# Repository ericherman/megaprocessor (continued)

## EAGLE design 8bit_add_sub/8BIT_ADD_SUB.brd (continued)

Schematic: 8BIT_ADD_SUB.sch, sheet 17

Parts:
D109, D110, D111, D112, D113, D114, D115, D116, D117: L-1334SRT; LED3MM
Q157, Q158, Q159, Q160, Q161, Q162, Q163, Q164, Q165: 2N7000; TO92-DGS
R181, R183, R186, R188, R191, R193: 10k; R_P2INCH
R182, R184, R185, R187, R189, R190, R192, R194, R195: 470; R_P2INCH

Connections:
+5V: D109.A, D110.A, D111.A, D112.A, D113.A, D114.A, D115.A, D116.A, D117.A, R181.2, R183.2, R186.2, R188.2, R191.2, R193.2; also elsewhere on the board
ADD_R4: Q158.G; also elsewhere on the board
ADD_R4_N: R185.1; also elsewhere on the board
CRY3: Q157.G; also elsewhere on the board
CRY3_N: R184.1; also elsewhere on the board
CRY4: Q162.D, R188.1; also elsewhere on the board
CRY4_N: Q160.D, Q161.D, Q162.G, R186.1, R187.1; also elsewhere on the board
GND: Q158.S, Q159.S, Q160.S, Q161.S, Q162.S, Q164.S, Q165.S; also elsewhere on the board
INV_B4: Q163.G; also elsewhere on the board
INV_B4_N: R194.1; also elsewhere on the board
IN_A4: Q164.G; also elsewhere on the board
IN_A4_N: R195.1; also elsewhere on the board
unnamed: Q157.S, Q158.D
unnamed: D109.K (C), R182.2
unnamed: Q159.D, Q160.G, R183.1
unnamed: Q157.D, Q159.G, R181.1, R182.1, R189.1
unnamed: D111.K (C), R185.2
unnamed: D110.K (C), R184.2
unnamed: D112.K (C), R187.2
unnamed: D114.K (C), R190.2
unnamed: D113.K (C), R189.2
unnamed: Q163.S, Q164.D
unnamed: D115.K (C), R192.2
unnamed: Q161.G, Q165.D, R193.1
unnamed: Q163.D, Q165.G, R190.1, R191.1, R192.1
unnamed: D117.K (C), R195.2
unnamed: D116.K (C), R194.2

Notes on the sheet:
ADD/SUB Bit 4 carry generation
AND
LED Y
LED A
LED B

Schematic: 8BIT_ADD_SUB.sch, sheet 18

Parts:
D73, D74, D75, D76, D77, D78: L-1334SRT; LED3MM
Q109, Q110, Q111, Q112, Q113, Q114, Q115, Q116, Q117, Q118: 2N7000; TO92-DGS
R121, R123, R126, R128: 10k; R_P2INCH
R122, R124, R125, R127, R129, R130: 470; R_P2INCH

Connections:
+5V: D73.A, D74.A, D75.A, D76.A, D77.A, D78.A, R121.2, R123.2, R126.2, R128.2; also elsewhere on the board
ADD_R5: Q113.D, Q117.G, R123.1; also elsewhere on the board
ADD_R5_N: Q109.D, Q111.D, Q113.G, Q115.G, R121.1, R122.1, R130.1; also elsewhere on the board
CRY4: Q114.G; also elsewhere on the board
CRY4_N: Q116.G, R129.1; also elsewhere on the board
GND: Q110.S, Q112.S, Q113.S, Q115.S, Q117.S, Q118.S; also elsewhere on the board
INV_B5: Q109.G; also elsewhere on the board
INV_B5_N: Q111.G, R124.1; also elsewhere on the board
IN_A5: Q112.G; also elsewhere on the board
IN_A5_N: Q110.G, R125.1; also elsewhere on the board
unnamed: Q109.S, Q110.D
unnamed: Q111.S, Q112.D
unnamed: D73.K (C), R122.2
unnamed: D75.K (C), R125.2
unnamed: D74.K (C), R124.2
unnamed: Q114.S, Q115.D
unnamed: Q116.S, Q117.D
unnamed: D76.K (C), R127.2
unnamed: D78.K (C), R130.2
unnamed: D77.K (C), R129.2
Y5: Q118.D, R128.1; also elsewhere on the board
Y5_N: Q114.D, Q116.D, Q118.G, R126.1, R127.1; also elsewhere on the board

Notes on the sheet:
ADD/SUB bit 5 XORs.
XOR
LED A
LED B
LED Y

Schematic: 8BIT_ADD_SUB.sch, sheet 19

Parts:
D118, D119, D120, D121, D122, D123, D124, D125, D126: L-1334SRT; LED3MM
Q166, Q167, Q168, Q169, Q170, Q171, Q172, Q173, Q174: 2N7000; TO92-DGS
R196, R198, R201, R203, R206, R208: 10k; R_P2INCH
R197, R199, R200, R202, R204, R205, R207, R209, R210: 470; R_P2INCH

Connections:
+5V: D118.A, D119.A, D120.A, D121.A, D122.A, D123.A, D124.A, D125.A, D126.A, R196.2, R198.2, R201.2, R203.2, R206.2, R208.2; also elsewhere on the board
ADD_R5: Q167.G; also elsewhere on the board
ADD_R5_N: R200.1; also elsewhere on the board
CRY4: Q166.G; also elsewhere on the board
CRY4_N: R199.1; also elsewhere on the board
CRY5: Q171.D, R203.1; also elsewhere on the board
CRY5_N: Q169.D, Q170.D, Q171.G, R201.1, R202.1; also elsewhere on the board
GND: Q167.S, Q168.S, Q169.S, Q170.S, Q171.S, Q173.S, Q174.S; also elsewhere on the board
INV_B5: Q172.G; also elsewhere on the board
INV_B5_N: R209.1; also elsewhere on the board
IN_A5: Q173.G; also elsewhere on the board
IN_A5_N: R210.1; also elsewhere on the board
unnamed: Q166.S, Q167.D
unnamed: D118.K (C), R197.2
unnamed: Q168.D, Q169.G, R198.1
unnamed: Q166.D, Q168.G, R196.1, R197.1, R204.1
unnamed: D120.K (C), R200.2
unnamed: D119.K (C), R199.2
unnamed: D121.K (C), R202.2
unnamed: D123.K (C), R205.2
unnamed: D122.K (C), R204.2
unnamed: Q172.S, Q173.D
unnamed: D124.K (C), R207.2
unnamed: Q170.G, Q174.D, R208.1
unnamed: Q172.D, Q174.G, R205.1, R206.1, R207.1
unnamed: D126.K (C), R210.2
unnamed: D125.K (C), R209.2

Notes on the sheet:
ADD/SUB Bit 5 carry generation
AND
LED Y
LED A
LED B

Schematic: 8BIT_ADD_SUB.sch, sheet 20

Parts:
D79, D80, D81, D82, D83, D84: L-1334SRT; LED3MM
Q119, Q120, Q121, Q122, Q123, Q124, Q125, Q126, Q127, Q128: 2N7000; TO92-DGS
R131, R133, R136, R138: 10k; R_P2INCH
R132, R134, R135, R137, R139, R140: 470; R_P2INCH

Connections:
+5V: D79.A, D80.A, D81.A, D82.A, D83.A, D84.A, R131.2, R133.2, R136.2, R138.2; also elsewhere on the board
ADD_R6: Q123.D, Q127.G, R133.1; also elsewhere on the board
ADD_R6_N: Q119.D, Q121.D, Q123.G, Q125.G, R131.1, R132.1, R140.1; also elsewhere on the board
CRY5: Q124.G; also elsewhere on the board
CRY5_N: Q126.G, R139.1; also elsewhere on the board
GND: Q120.S, Q122.S, Q123.S, Q125.S, Q127.S, Q128.S; also elsewhere on the board
INV_B6: Q119.G; also elsewhere on the board
INV_B6_N: Q121.G, R134.1; also elsewhere on the board
IN_A6: Q122.G; also elsewhere on the board
IN_A6_N: Q120.G, R135.1; also elsewhere on the board
unnamed: Q119.S, Q120.D
unnamed: Q121.S, Q122.D
unnamed: D79.K (C), R132.2
unnamed: D81.K (C), R135.2
unnamed: D80.K (C), R134.2
unnamed: Q124.S, Q125.D
unnamed: Q126.S, Q127.D
unnamed: D82.K (C), R137.2
unnamed: D84.K (C), R140.2
unnamed: D83.K (C), R139.2
Y6: Q128.D, R138.1; also elsewhere on the board
Y6_N: Q124.D, Q126.D, Q128.G, R136.1, R137.1; also elsewhere on the board

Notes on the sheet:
ADD/SUB bit 6 XORs.
XOR
LED A
LED B
LED Y

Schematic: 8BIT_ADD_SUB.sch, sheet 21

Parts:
D127, D128, D129, D130, D131, D132, D133, D134, D135: L-1334SRT; LED3MM
Q175, Q176, Q177, Q178, Q179, Q180, Q181, Q182, Q183: 2N7000; TO92-DGS
R211, R213, R216, R218, R221, R223: 10k; R_P2INCH
R212, R214, R215, R217, R219, R220, R222, R224, R225: 470; R_P2INCH

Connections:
+5V: D127.A, D128.A, D129.A, D130.A, D131.A, D132.A, D133.A, D134.A, D135.A, R211.2, R213.2, R216.2, R218.2, R221.2, R223.2; also elsewhere on the board
ADD_R6: Q176.G; also elsewhere on the board
ADD_R6_N: R215.1; also elsewhere on the board
CRY5: Q175.G; also elsewhere on the board
CRY5_N: R214.1; also elsewhere on the board
CRY6: Q180.D, R218.1; also elsewhere on the board
CRY6_N: Q178.D, Q179.D, Q180.G, R216.1, R217.1; also elsewhere on the board
GND: Q176.S, Q177.S, Q178.S, Q179.S, Q180.S, Q182.S, Q183.S; also elsewhere on the board
INV_B6: Q181.G; also elsewhere on the board
INV_B6_N: R224.1; also elsewhere on the board
IN_A6: Q182.G; also elsewhere on the board
IN_A6_N: R225.1; also elsewhere on the board
unnamed: Q175.S, Q176.D
unnamed: D127.K (C), R212.2
unnamed: Q177.D, Q178.G, R213.1
unnamed: Q175.D, Q177.G, R211.1, R212.1, R219.1
unnamed: D129.K (C), R215.2
unnamed: D128.K (C), R214.2
unnamed: D130.K (C), R217.2
unnamed: D132.K (C), R220.2
unnamed: D131.K (C), R219.2
unnamed: Q181.S, Q182.D
unnamed: D133.K (C), R222.2
unnamed: Q179.G, Q183.D, R223.1
unnamed: Q181.D, Q183.G, R220.1, R221.1, R222.1
unnamed: D135.K (C), R225.2
unnamed: D134.K (C), R224.2

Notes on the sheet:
ADD/SUB Bit 6 carry generation
AND
LED Y
LED A
LED B

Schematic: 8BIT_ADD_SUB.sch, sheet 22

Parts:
D85, D86, D87, D88, D89, D90: L-1334SRT; LED3MM
Q129, Q130, Q131, Q132, Q133, Q134, Q135, Q136, Q137, Q138: 2N7000; TO92-DGS
R141, R143, R146, R148: 10k; R_P2INCH
R142, R144, R145, R147, R149, R150: 470; R_P2INCH

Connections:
+5V: D85.A, D86.A, D87.A, D88.A, D89.A, D90.A, R141.2, R143.2, R146.2, R148.2; also elsewhere on the board
ADD_R7: Q133.D, Q137.G, R143.1; also elsewhere on the board
ADD_R7_N: Q129.D, Q131.D, Q133.G, Q135.G, R141.1, R142.1, R150.1; also elsewhere on the board
CRY6: Q134.G; also elsewhere on the board
CRY6_N: Q136.G, R149.1; also elsewhere on the board
GND: Q130.S, Q132.S, Q133.S, Q135.S, Q137.S, Q138.S; also elsewhere on the board
INV_B7: Q129.G; also elsewhere on the board
INV_B7_N: Q131.G, R144.1; also elsewhere on the board
IN_A7: Q132.G; also elsewhere on the board
IN_A7_N: Q130.G, R145.1; also elsewhere on the board
unnamed: Q129.S, Q130.D
unnamed: Q131.S, Q132.D
unnamed: D85.K (C), R142.2
unnamed: D87.K (C), R145.2
unnamed: D86.K (C), R144.2
unnamed: Q134.S, Q135.D
unnamed: Q136.S, Q137.D
unnamed: D88.K (C), R147.2
unnamed: D90.K (C), R150.2
unnamed: D89.K (C), R149.2
Y7: Q138.D, R148.1; also elsewhere on the board
Y7_N: Q134.D, Q136.D, Q138.G, R146.1, R147.1; also elsewhere on the board

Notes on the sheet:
ADD/SUB bit 7 XORs.
XOR
LED A
LED B
LED Y

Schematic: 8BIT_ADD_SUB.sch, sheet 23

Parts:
D136, D137, D138, D139, D140, D141, D142, D143, D144: L-1334SRT; LED3MM
Q184, Q185, Q186, Q187, Q188, Q189, Q190, Q191, Q192: 2N7000; TO92-DGS
R226, R228, R231, R233, R236, R238: 10k; R_P2INCH
R227, R229, R230, R232, R234, R235, R237, R239, R240: 470; R_P2INCH

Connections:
+5V: D136.A, D137.A, D138.A, D139.A, D140.A, D141.A, D142.A, D143.A, D144.A, R226.2, R228.2, R231.2, R233.2, R236.2, R238.2; also elsewhere on the board
ADD_R7: Q185.G; also elsewhere on the board
ADD_R7_N: R230.1; also elsewhere on the board
CARRY_OUT: Q189.D, R233.1; also elsewhere on the board
CARRY_OUT_N: Q187.D, Q188.D, Q189.G, R231.1, R232.1
CRY6: Q184.G; also elsewhere on the board
CRY6_N: R229.1; also elsewhere on the board
GND: Q185.S, Q186.S, Q187.S, Q188.S, Q189.S, Q191.S, Q192.S; also elsewhere on the board
INV_B7: Q190.G; also elsewhere on the board
INV_B7_N: R239.1; also elsewhere on the board
IN_A7: Q191.G; also elsewhere on the board
IN_A7_N: R240.1; also elsewhere on the board
unnamed: Q184.S, Q185.D
unnamed: D136.K (C), R227.2
unnamed: Q186.D, Q187.G, R228.1
unnamed: Q184.D, Q186.G, R226.1, R227.1, R234.1
unnamed: D138.K (C), R230.2
unnamed: D137.K (C), R229.2
unnamed: D139.K (C), R232.2
unnamed: D141.K (C), R235.2
unnamed: D140.K (C), R234.2
unnamed: Q190.S, Q191.D
unnamed: D142.K (C), R237.2
unnamed: Q188.G, Q192.D, R238.1
unnamed: Q190.D, Q192.G, R235.1, R236.1, R237.1
unnamed: D144.K (C), R240.2
unnamed: D143.K (C), R239.2

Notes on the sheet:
ADD/SUB Bit 7 carry generation
AND
LED Y
LED A
LED B

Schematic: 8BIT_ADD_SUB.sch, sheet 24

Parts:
D154, D163, D164, D165, D166, D167, D168, D169, D170, D171, D172: L-1334SRT; LED3MM
Q209, Q210, Q211, Q212, Q213: 2N7000; TO92-DGS
R257, R268, R285, R287, R289: 10k; R_P2INCH
R258, R277, R278, R279, R280, R281, R282, R283, R284, R286, R288: 470; R_P2INCH

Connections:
+5V: D154.A, D163.A, D164.A, D165.A, D166.A, D167.A, D168.A, D169.A, D170.A, D171.A, D172.A, R257.2, R268.2, R285.2, R287.2, R289.2; also elsewhere on the board
CARRY_IN: Q213.D, R289.1; also elsewhere on the board
CARRY_IN_N: Q212.D, Q213.G, R285.1, R288.1; also elsewhere on the board
CARRY_IN_RAW: Q212.G; also elsewhere on the board
CARRY_OUT: Q211.G; also elsewhere on the board
CARRY_OUT_N2: Q211.D, R286.1, R287.1
DO_INVERT: Q210.D, R268.1; also elsewhere on the board
DO_INVERT_N: Q209.D, Q210.G, R257.1, R258.1; also elsewhere on the board
DO_INVERT_RAW: Q209.G; also elsewhere on the board
GND: Q209.S, Q210.S, Q211.S, Q212.S, Q213.S; also elsewhere on the board
unnamed: D154.K (C), R258.2
unnamed: D163.K (C), R277.2
unnamed: D171.K (C), R288.2
unnamed: D164.K (C), R278.2
unnamed: D165.K (C), R279.2
unnamed: D166.K (C), R280.2
unnamed: D167.K (C), R281.2
unnamed: D168.K (C), R282.2
unnamed: D169.K (C), R283.2
unnamed: D170.K (C), R284.2
unnamed: D172.K (C), R286.2
Y0_N: R277.1; also elsewhere on the board
Y1_N: R278.1; also elsewhere on the board
Y2_N: R279.1; also elsewhere on the board
Y3_N: R280.1; also elsewhere on the board
Y4_N: R281.1; also elsewhere on the board
Y5_N: R282.1; also elsewhere on the board
Y6_N: R283.1; also elsewhere on the board
Y7_N: R284.1; also elsewhere on the board

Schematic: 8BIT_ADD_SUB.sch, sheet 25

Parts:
J4: 30_HDR_LOCKING_RA

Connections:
GND: J4.1, J4.10, J4.19, J4.28; also elsewhere on the board
IN_A0: J4.2; also elsewhere on the board
IN_A1: J4.3; also elsewhere on the board
IN_A2: J4.4; also elsewhere on the board
IN_A3: J4.5; also elsewhere on the board
IN_A4: J4.6; also elsewhere on the board
IN_A5: J4.7; also elsewhere on the board
IN_A6: J4.8; also elsewhere on the board
IN_A7: J4.9; also elsewhere on the board
IN_B0: J4.11; also elsewhere on the board
IN_B1: J4.12; also elsewhere on the board
IN_B2: J4.13; also elsewhere on the board
IN_B3: J4.14; also elsewhere on the board
IN_B4: J4.15; also elsewhere on the board
IN_B5: J4.16; also elsewhere on the board
IN_B6: J4.17; also elsewhere on the board
IN_B7: J4.18; also elsewhere on the board
Y0: J4.20; also elsewhere on the board
Y1: J4.21; also elsewhere on the board
Y2: J4.22; also elsewhere on the board
Y3: J4.23; also elsewhere on the board
Y4: J4.24; also elsewhere on the board
Y5: J4.25; also elsewhere on the board
Y6: J4.26; also elsewhere on the board
Y7: J4.27; also elsewhere on the board

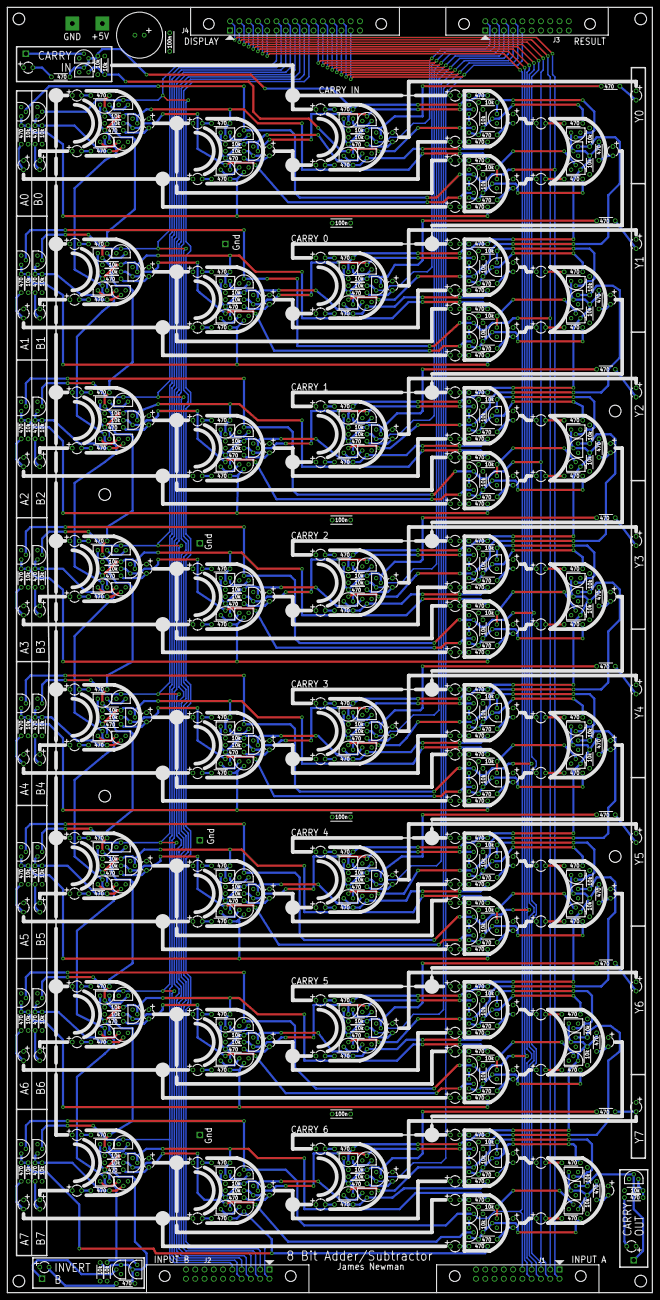
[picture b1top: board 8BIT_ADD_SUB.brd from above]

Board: 4 copper layers, 176.5 x 351.8 mm, 699 parts (0 on the bottom side), 372 nets.

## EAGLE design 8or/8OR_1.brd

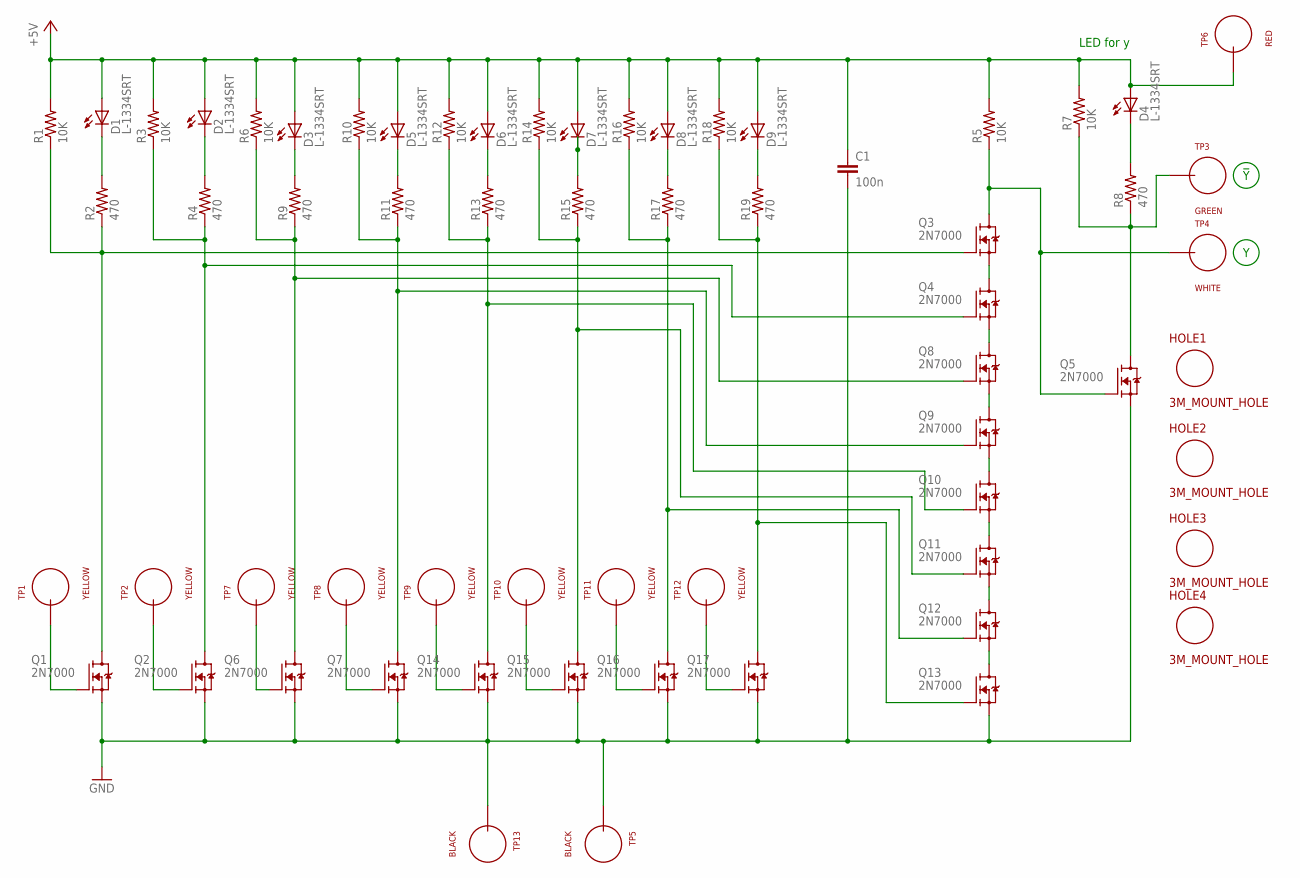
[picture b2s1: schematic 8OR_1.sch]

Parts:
C1: 100n; CAP_P2INCH
D1, D2, D3, D4, D5, D6, D7, D8, D9: L-1334SRT; LED3MM
HOLE1, HOLE2, HOLE3, HOLE4: 3M_MOUNT_HOLE; 3M_HOLE
Q1, Q2, Q3, Q4, Q5, Q6, Q7, Q8, Q9, Q10, Q11, Q12, Q13, Q14, Q15, Q16, Q17: 2N7000; TO92-DGS
R1, R3, R5, R6, R7, R10, R12, R14, R16, R18: 10K; R_P2INCH
R2, R4, R8, R9, R11, R13, R15, R17, R19: 470; R_P2INCH
TP1, TP2, TP7, TP8, TP9, TP10, TP11, TP12: YELLOW; TEST_LOOP
TP3: GREEN; TEST_LOOP
TP4: WHITE; TEST_LOOP
TP5, TP13: BLACK; TEST_LOOP
TP6: RED; TEST_LOOP

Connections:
+5V: C1.1, D1.A, D2.A, D3.A, D4.A, D5.A, D6.A, D7.A, D8.A, D9.A, R1.2, R3.2, R5.2, R6.2, R7.2, R10.2, R12.2, R14.2, R16.2, R18.2, TP6.P$1
GND: C1.2, Q1.S, Q2.S, Q5.S, Q6.S, Q7.S, Q13.S, Q14.S, Q15.S, Q16.S, Q17.S, TP5.P$1, TP13.P$1
unnamed: Q3.D, Q5.G, R5.1, TP4.P$1
unnamed: Q3.S, Q4.D
unnamed: D4.K (C), R8.2
unnamed: Q5.D, R7.1, R8.1, TP3.P$1
unnamed: D5.K (C), R11.2
unnamed: D2.K (C), R4.2
unnamed: Q4.S, Q8.D
unnamed: D1.K (C), R2.2
unnamed: Q1.D, Q3.G, R1.1, R2.1
unnamed: D3.K (C), R9.2
unnamed: Q1.G, TP1.P$1
unnamed: Q2.G, TP2.P$1
unnamed: Q6.D, Q8.G, R6.1, R9.1
unnamed: Q9.S, Q10.D
unnamed: Q10.S, Q11.D
unnamed: Q7.D, Q9.G, R10.1, R11.1
unnamed: Q2.D, Q4.G, R3.1, R4.1
unnamed: Q8.S, Q9.D
unnamed: D6.K (C), R13.2
unnamed: D7.K (C), R15.2
unnamed: D8.K (C), R17.2
unnamed: D9.K (C), R19.2
unnamed: Q10.G, Q14.D, R12.1, R13.1
unnamed: Q11.G, Q15.D, R14.1, R15.1
unnamed: Q12.G, Q16.D, R16.1, R17.1
unnamed: Q13.G, Q17.D, R18.1, R19.1
unnamed: Q11.S, Q12.D
unnamed: Q12.S, Q13.D
unnamed: Q17.G, TP12.P$1
unnamed: Q16.G, TP11.P$1
unnamed: Q15.G, TP10.P$1
unnamed: Q14.G, TP9.P$1
unnamed: Q7.G, TP8.P$1
unnamed: Q6.G, TP7.P$1

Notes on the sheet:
LED for y

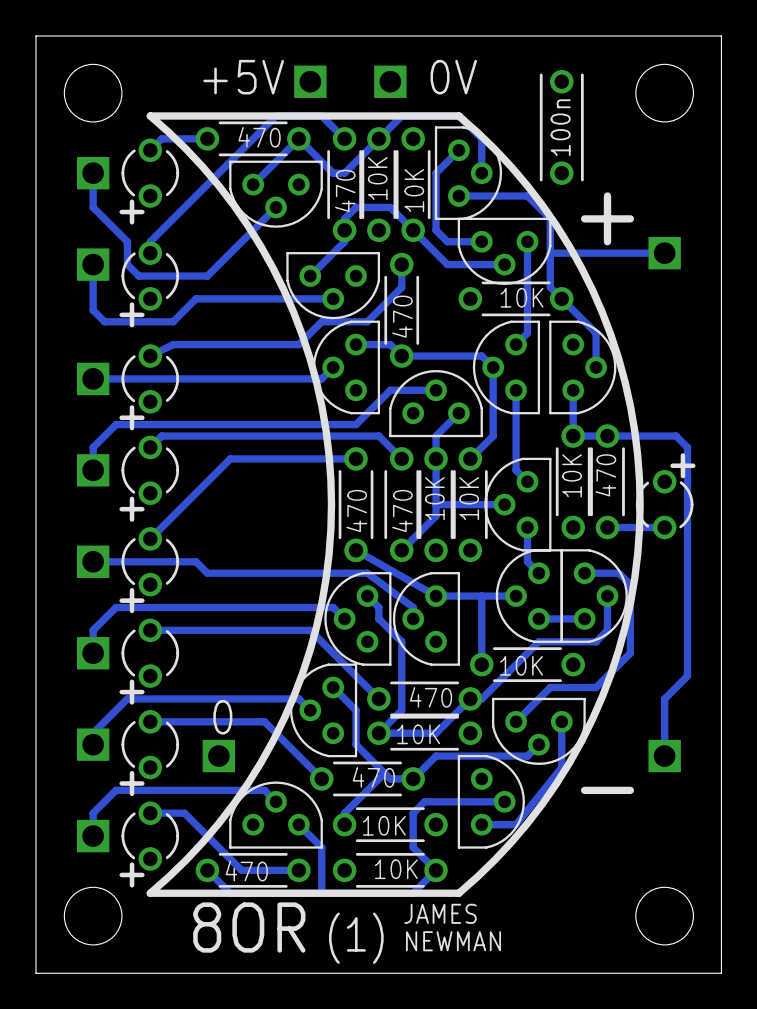
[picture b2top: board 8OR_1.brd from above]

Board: 4 copper layers, 38.1 x 52.1 mm, 63 parts (0 on the bottom side), 36 nets.

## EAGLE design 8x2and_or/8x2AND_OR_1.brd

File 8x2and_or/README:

8x2AND OR

Somehow when doing this board I messed up the power plane so it didn't
extend over the whole board. So there's a few wires underneath to sort
things out.

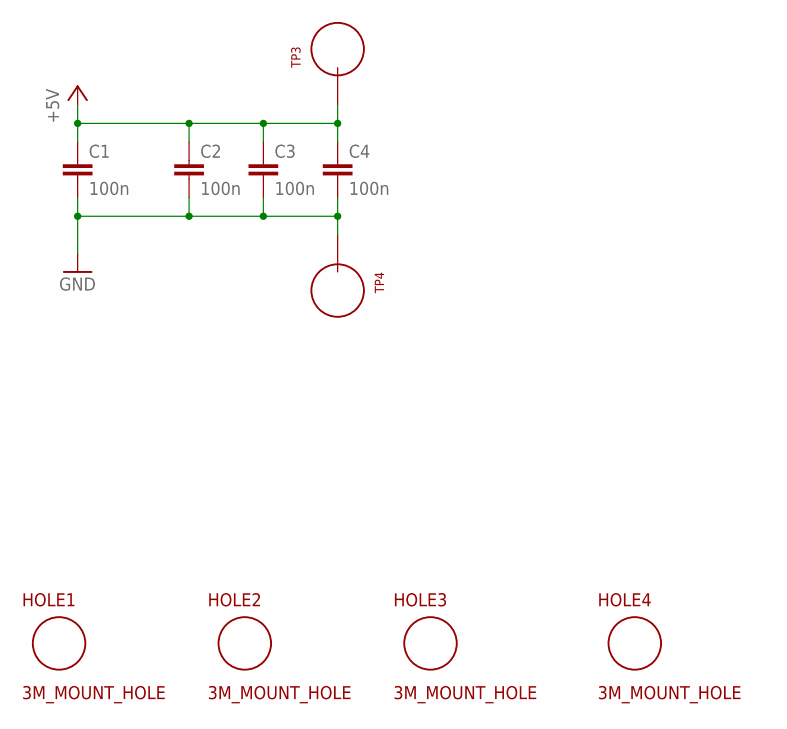
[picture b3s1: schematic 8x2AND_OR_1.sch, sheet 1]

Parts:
C1, C2, C3, C4: 100n; CAP_P2INCH
HOLE1, HOLE2, HOLE3, HOLE4: 3M_MOUNT_HOLE; 3M_HOLE
TP3, TP4: TEST_LOOP

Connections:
+5V: C1.1, C2.1, C3.1, C4.1, TP3.P$1; also elsewhere on the board
GND: C1.2, C2.2, C3.2, C4.2, TP4.P$1; also elsewhere on the board

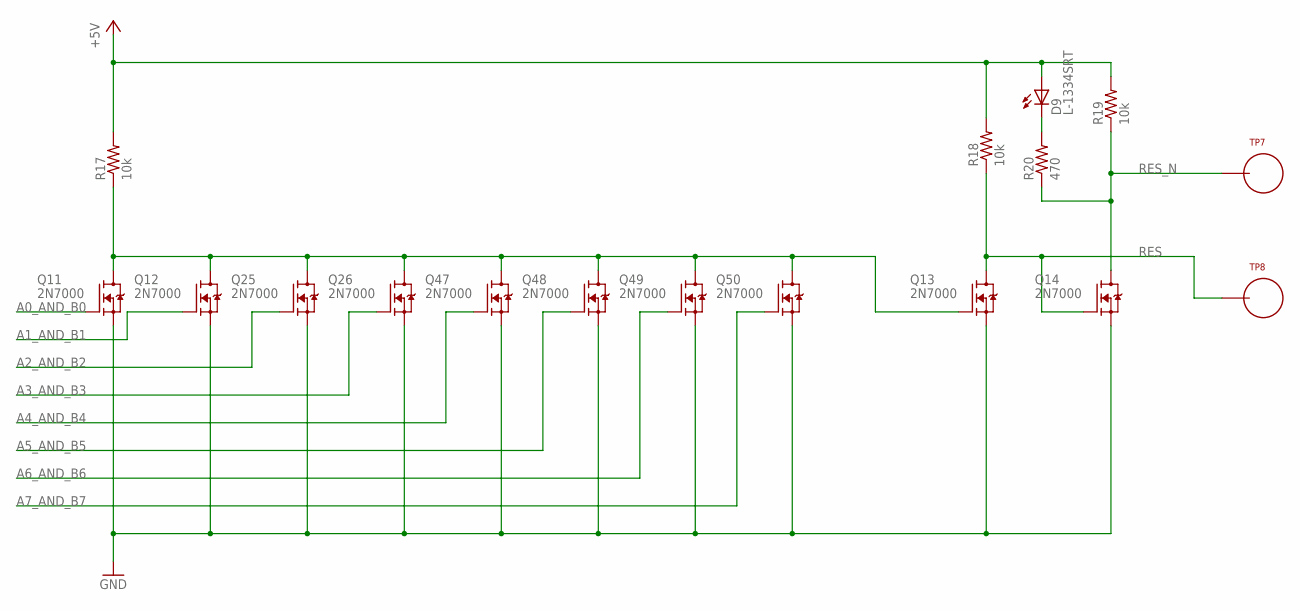
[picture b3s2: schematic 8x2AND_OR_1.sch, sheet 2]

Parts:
D9: L-1334SRT; LED3MM
Q11, Q12, Q13, Q14, Q25, Q26, Q47, Q48, Q49, Q50: 2N7000; TO92-DGS
R17, R18, R19: 10k; R_P2INCH
R20: 470; R_P2INCH
TP7, TP8: TEST_LOOP

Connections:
+5V: D9.A, R17.2, R18.2, R19.2; also elsewhere on the board
A0_AND_B0: Q11.G; also elsewhere on the board
A1_AND_B1: Q12.G; also elsewhere on the board
A2_AND_B2: Q25.G; also elsewhere on the board
A3_AND_B3: Q26.G; also elsewhere on the board
A4_AND_B4: Q47.G; also elsewhere on the board
A5_AND_B5: Q48.G; also elsewhere on the board
A6_AND_B6: Q49.G; also elsewhere on the board
A7_AND_B7: Q50.G; also elsewhere on the board
GND: Q11.S, Q12.S, Q13.S, Q14.S, Q25.S, Q26.S, Q47.S, Q48.S, Q49.S, Q50.S; also elsewhere on the board
unnamed: Q11.D, Q12.D, Q13.G, Q25.D, Q26.D, Q47.D, Q48.D, Q49.D, Q50.D, R17.1
unnamed: D9.K (C), R20.2
RES: Q13.D, Q14.G, R18.1, TP8.P$1
RES_N: Q14.D, R19.1, R20.1, TP7.P$1

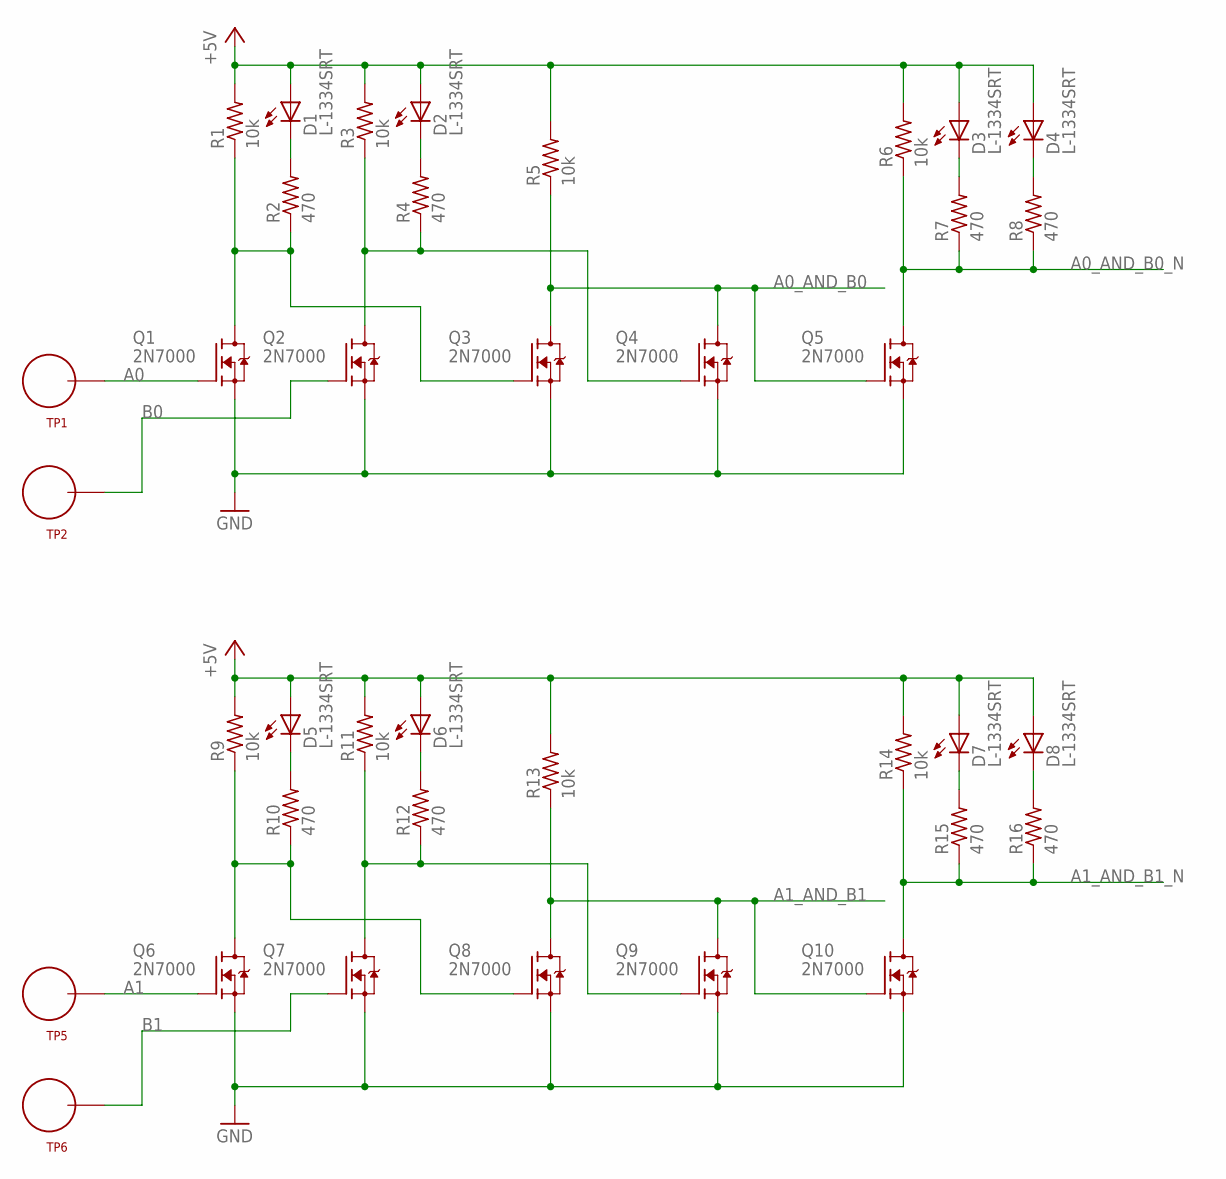
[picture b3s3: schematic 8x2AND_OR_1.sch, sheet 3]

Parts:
D1, D2, D3, D4, D5, D6, D7, D8: L-1334SRT; LED3MM
Q1, Q2, Q3, Q4, Q5, Q6, Q7, Q8, Q9, Q10: 2N7000; TO92-DGS
R1, R3, R5, R6, R9, R11, R13, R14: 10k; R_P2INCH
R2, R4, R7, R8, R10, R12, R15, R16: 470; R_P2INCH
TP1, TP2, TP5, TP6: TEST_LOOP

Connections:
+5V: D1.A, D2.A, D3.A, D4.A, D5.A, D6.A, D7.A, D8.A, R1.2, R3.2, R5.2, R6.2, R9.2, R11.2, R13.2, R14.2; also elsewhere on the board
A0: Q1.G, TP1.P$1
A0_AND_B0: Q3.D, Q4.D, Q5.G, R5.1; also elsewhere on the board
A0_AND_B0_N: Q5.D, R6.1, R7.1, R8.1
A1: Q6.G, TP5.P$1
A1_AND_B1: Q8.D, Q9.D, Q10.G, R13.1; also elsewhere on the board
A1_AND_B1_N: Q10.D, R14.1, R15.1, R16.1
B0: Q2.G, TP2.P$1
B1: Q7.G, TP6.P$1
GND: Q1.S, Q2.S, Q3.S, Q4.S, Q5.S, Q6.S, Q7.S, Q8.S, Q9.S, Q10.S; also elsewhere on the board
unnamed: D1.K (C), R2.2
unnamed: Q1.D, Q3.G, R1.1, R2.1
unnamed: D4.K (C), R8.2
unnamed: D2.K (C), R4.2
unnamed: Q2.D, Q4.G, R3.1, R4.1
unnamed: D5.K (C), R10.2
unnamed: Q6.D, Q8.G, R9.1, R10.1
unnamed: D6.K (C), R12.2
unnamed: D3.K (C), R7.2
unnamed: Q7.D, Q9.G, R11.1, R12.1
unnamed: D7.K (C), R15.2
unnamed: D8.K (C), R16.2

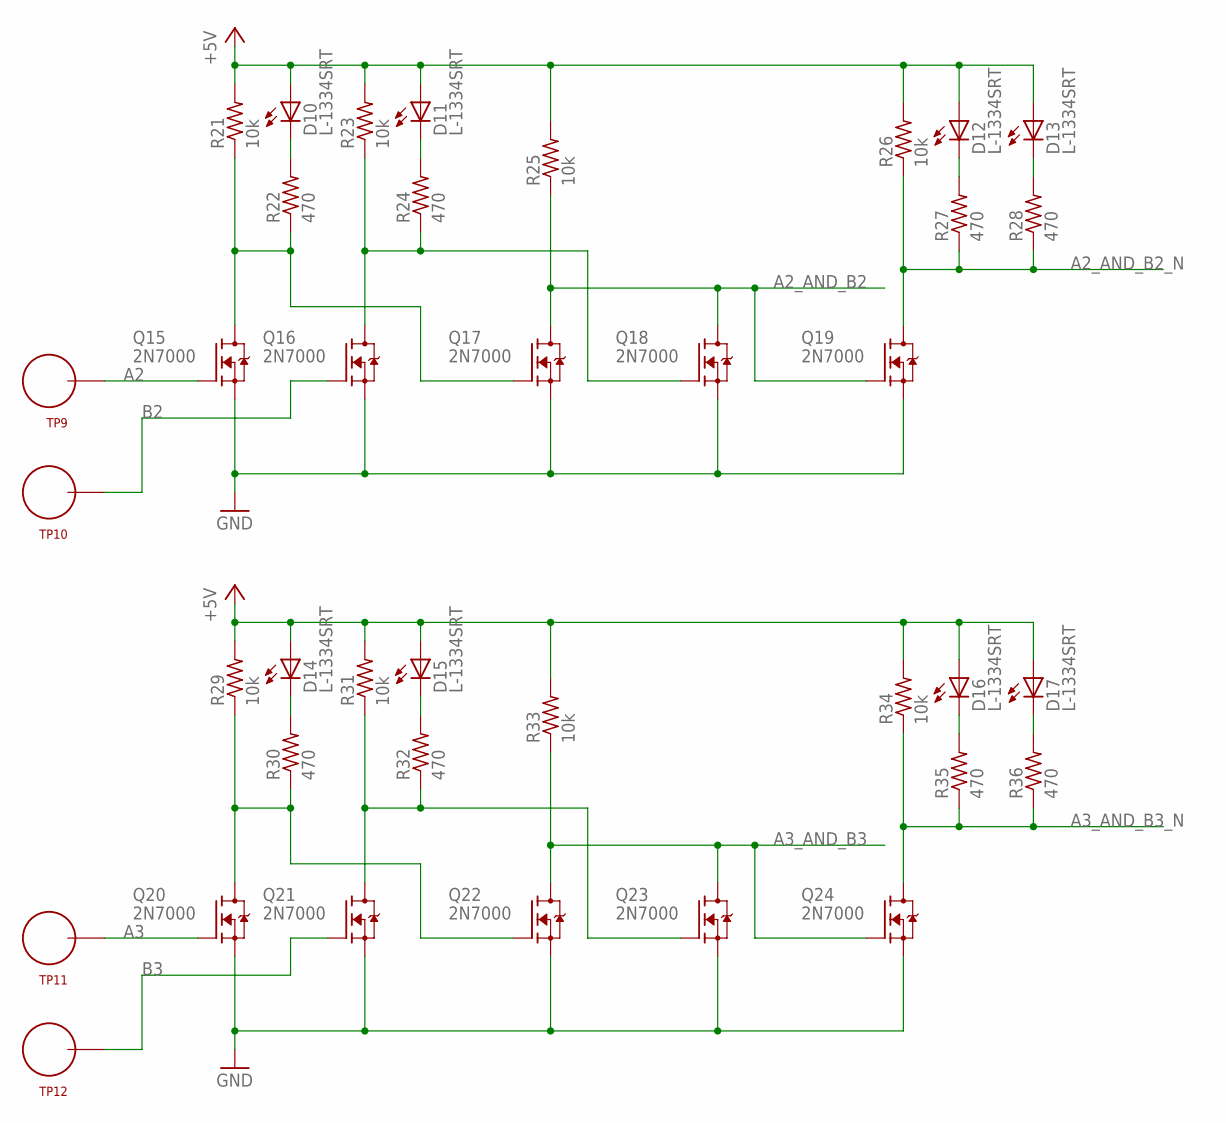
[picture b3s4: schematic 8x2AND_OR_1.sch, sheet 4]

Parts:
D10, D11, D12, D13, D14, D15, D16, D17: L-1334SRT; LED3MM
Q15, Q16, Q17, Q18, Q19, Q20, Q21, Q22, Q23, Q24: 2N7000; TO92-DGS
R21, R23, R25, R26, R29, R31, R33, R34: 10k; R_P2INCH
R22, R24, R27, R28, R30, R32, R35, R36: 470; R_P2INCH
TP9, TP10, TP11, TP12: TEST_LOOP

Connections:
+5V: D10.A, D11.A, D12.A, D13.A, D14.A, D15.A, D16.A, D17.A, R21.2, R23.2, R25.2, R26.2, R29.2, R31.2, R33.2, R34.2; also elsewhere on the board
A2: Q15.G, TP9.P$1
A2_AND_B2: Q17.D, Q18.D, Q19.G, R25.1; also elsewhere on the board
A2_AND_B2_N: Q19.D, R26.1, R27.1, R28.1
A3: Q20.G, TP11.P$1
A3_AND_B3: Q22.D, Q23.D, Q24.G, R33.1; also elsewhere on the board
A3_AND_B3_N: Q24.D, R34.1, R35.1, R36.1
B2: Q16.G, TP10.P$1
B3: Q21.G, TP12.P$1
GND: Q15.S, Q16.S, Q17.S, Q18.S, Q19.S, Q20.S, Q21.S, Q22.S, Q23.S, Q24.S; also elsewhere on the board
unnamed: D10.K (C), R22.2
unnamed: Q15.D, Q17.G, R21.1, R22.1
unnamed: D11.K (C), R24.2
unnamed: Q16.D, Q18.G, R23.1, R24.1
unnamed: D12.K (C), R27.2
unnamed: D13.K (C), R28.2
unnamed: D14.K (C), R30.2
unnamed: Q20.D, Q22.G, R29.1, R30.1
unnamed: D15.K (C), R32.2
unnamed: Q21.D, Q23.G, R31.1, R32.1
unnamed: D16.K (C), R35.2
unnamed: D17.K (C), R36.2

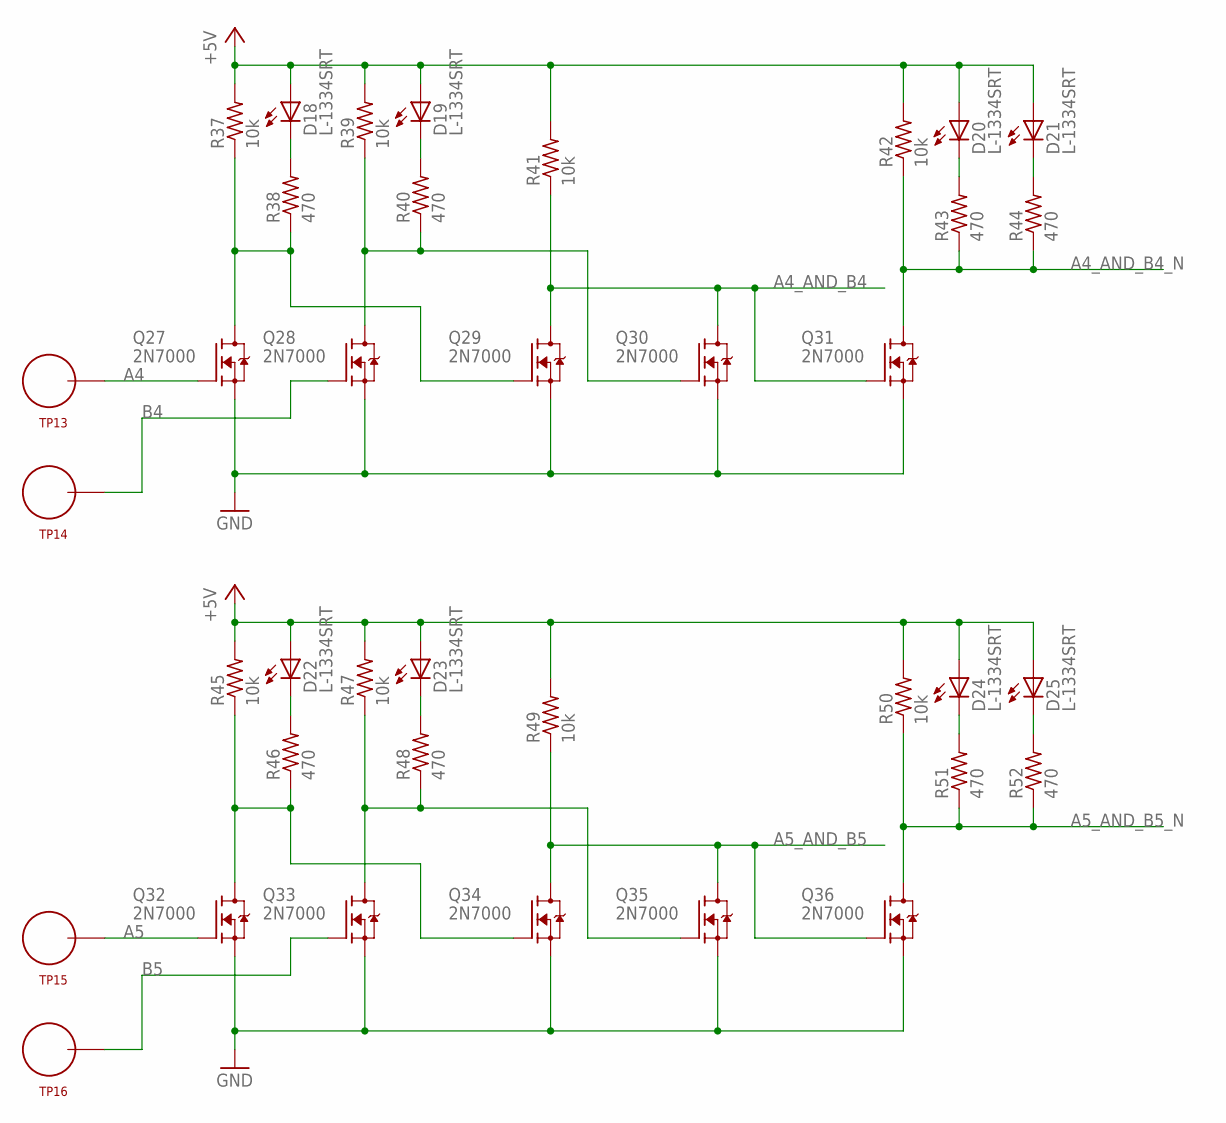
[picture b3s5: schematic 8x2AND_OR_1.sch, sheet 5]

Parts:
D18, D19, D20, D21, D22, D23, D24, D25: L-1334SRT; LED3MM
Q27, Q28, Q29, Q30, Q31, Q32, Q33, Q34, Q35, Q36: 2N7000; TO92-DGS
R37, R39, R41, R42, R45, R47, R49, R50: 10k; R_P2INCH
R38, R40, R43, R44, R46, R48, R51, R52: 470; R_P2INCH
TP13, TP14, TP15, TP16: TEST_LOOP

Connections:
+5V: D18.A, D19.A, D20.A, D21.A, D22.A, D23.A, D24.A, D25.A, R37.2, R39.2, R41.2, R42.2, R45.2, R47.2, R49.2, R50.2; also elsewhere on the board
A4: Q27.G, TP13.P$1
A4_AND_B4: Q29.D, Q30.D, Q31.G, R41.1; also elsewhere on the board
A4_AND_B4_N: Q31.D, R42.1, R43.1, R44.1
A5: Q32.G, TP15.P$1
A5_AND_B5: Q34.D, Q35.D, Q36.G, R49.1; also elsewhere on the board
A5_AND_B5_N: Q36.D, R50.1, R51.1, R52.1
B4: Q28.G, TP14.P$1
B5: Q33.G, TP16.P$1
GND: Q27.S, Q28.S, Q29.S, Q30.S, Q31.S, Q32.S, Q33.S, Q34.S, Q35.S, Q36.S; also elsewhere on the board
unnamed: D18.K (C), R38.2
unnamed: Q27.D, Q29.G, R37.1, R38.1
unnamed: D19.K (C), R40.2
unnamed: Q28.D, Q30.G, R39.1, R40.1
unnamed: D20.K (C), R43.2
unnamed: D21.K (C), R44.2
unnamed: D22.K (C), R46.2
unnamed: Q32.D, Q34.G, R45.1, R46.1
unnamed: D23.K (C), R48.2
unnamed: Q33.D, Q35.G, R47.1, R48.1
unnamed: D24.K (C), R51.2
unnamed: D25.K (C), R52.2

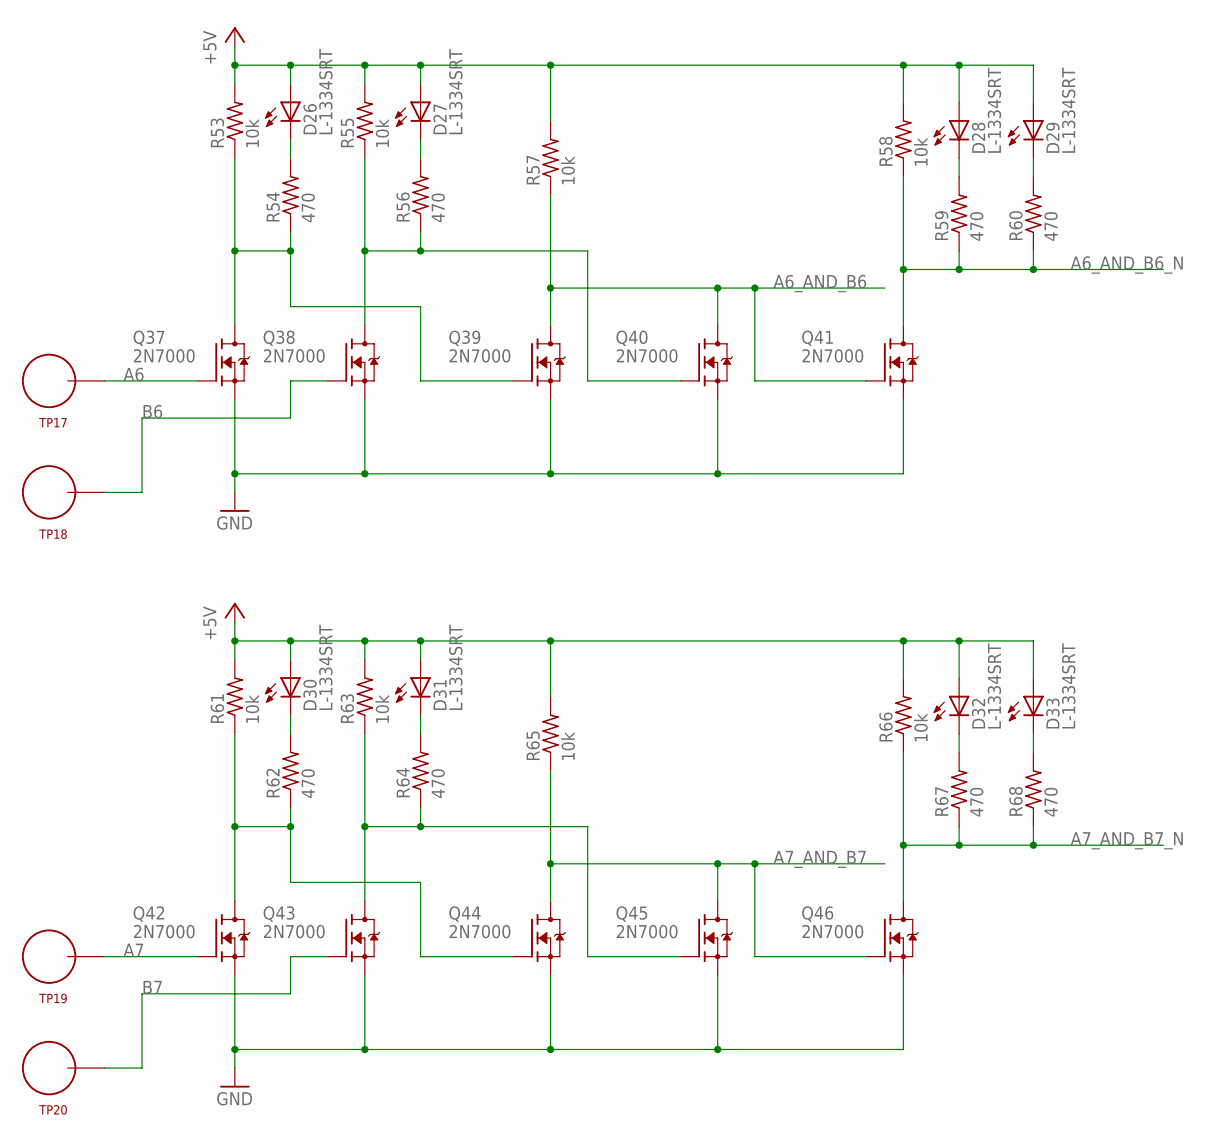
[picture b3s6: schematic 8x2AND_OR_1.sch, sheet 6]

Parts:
D26, D27, D28, D29, D30, D31, D32, D33: L-1334SRT; LED3MM
Q37, Q38, Q39, Q40, Q41, Q42, Q43, Q44, Q45, Q46: 2N7000; TO92-DGS
R53, R55, R57, R58, R61, R63, R65, R66: 10k; R_P2INCH
R54, R56, R59, R60, R62, R64, R67, R68: 470; R_P2INCH
TP17, TP18, TP19, TP20: TEST_LOOP

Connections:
+5V: D26.A, D27.A, D28.A, D29.A, D30.A, D31.A, D32.A, D33.A, R53.2, R55.2, R57.2, R58.2, R61.2, R63.2, R65.2, R66.2; also elsewhere on the board
A6: Q37.G, TP17.P$1
A6_AND_B6: Q39.D, Q40.D, Q41.G, R57.1; also elsewhere on the board
A6_AND_B6_N: Q41.D, R58.1, R59.1, R60.1
A7: Q42.G, TP19.P$1
A7_AND_B7: Q44.D, Q45.D, Q46.G, R65.1; also elsewhere on the board
A7_AND_B7_N: Q46.D, R66.1, R67.1, R68.1
B6: Q38.G, TP18.P$1
B7: Q43.G, TP20.P$1
GND: Q37.S, Q38.S, Q39.S, Q40.S, Q41.S, Q42.S, Q43.S, Q44.S, Q45.S, Q46.S; also elsewhere on the board
unnamed: D26.K (C), R54.2
unnamed: Q37.D, Q39.G, R53.1, R54.1
unnamed: D27.K (C), R56.2
unnamed: Q38.D, Q40.G, R55.1, R56.1
unnamed: D28.K (C), R59.2
unnamed: D29.K (C), R60.2
unnamed: D30.K (C), R62.2
unnamed: Q42.D, Q44.G, R61.1, R62.1
unnamed: D31.K (C), R64.2
unnamed: Q43.D, Q45.G, R63.1, R64.1
unnamed: D32.K (C), R67.2
unnamed: D33.K (C), R68.2
